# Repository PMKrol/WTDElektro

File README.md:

# WTDElektro
Scripts and software for laptops

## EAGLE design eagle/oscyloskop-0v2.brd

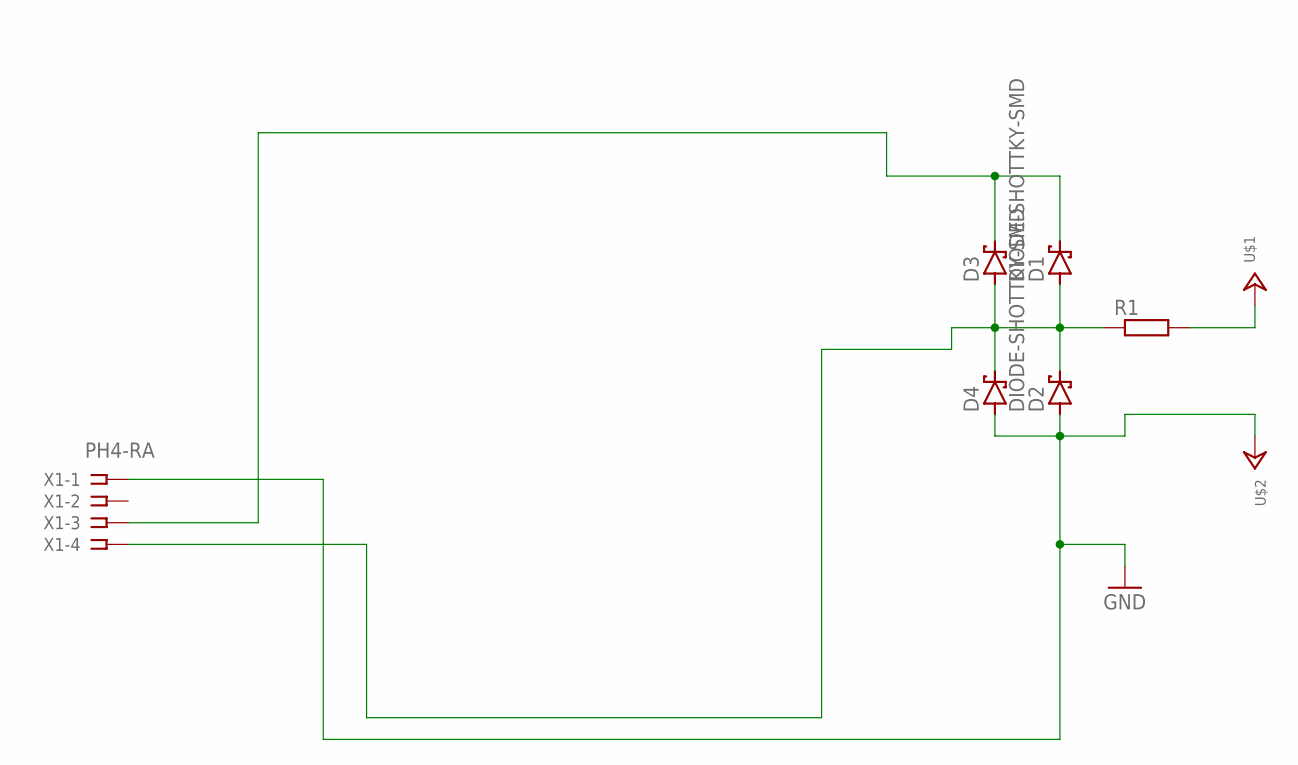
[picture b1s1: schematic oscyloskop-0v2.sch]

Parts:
D1, D2: DIODE-SHOTTKY-THT; DO41-7.6
D3, D4: DIODE-SHOTTKY-SMD; SOD123
R1: R0204/7; 0204/7
U$1, U$2: CON-BANANA; BANANA
X1: PH4-RA; SSW-104-02-G-S-RA

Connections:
GND: D2.A, D4.A, U$2.P$1, X1.1
unnamed: D1.C, D3.C, X1.3
unnamed: D1.A, D2.C, D3.A, D4.C, R1.1, X1.4
unnamed: R1.2, U$1.P$1

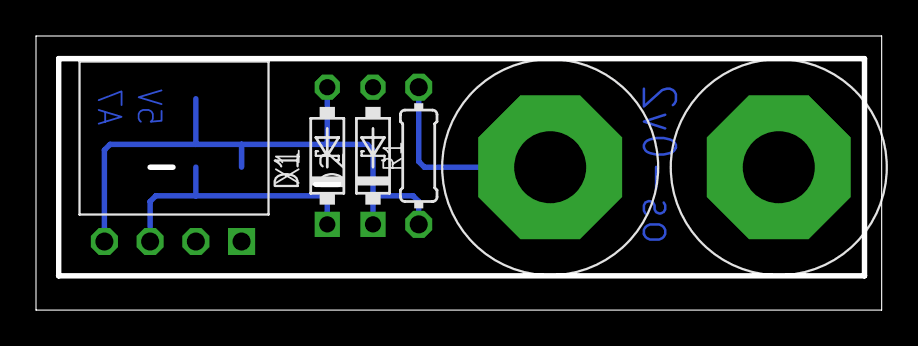
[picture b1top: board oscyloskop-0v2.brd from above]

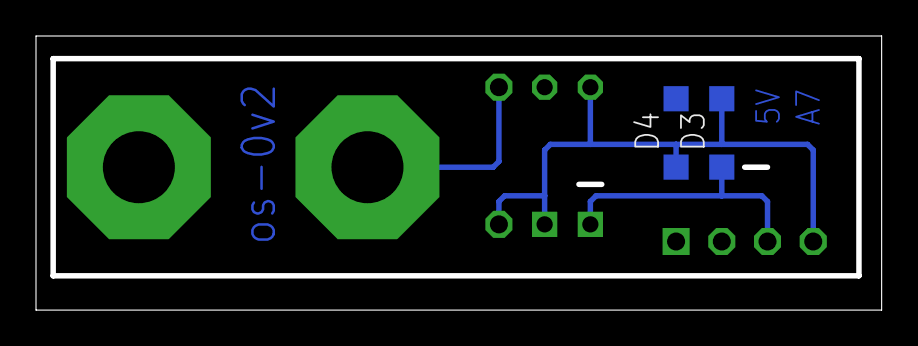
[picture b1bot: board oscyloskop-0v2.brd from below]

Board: 2 copper layers, 46.7 x 14.9 mm, 8 parts (2 on the bottom side), 4 nets.

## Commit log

2022-12-16 Add files via upload
    Original instruction from https://www.hackster.io/Ameduino/diy-arduino-oscilloscope-844fa3
2022-12-16 Add files via upload
    Eagle schematics. Libraries available at: https://github.com/PMKrol/WTDAutomatyka/tree/main/EAGLE/libraries
2022-12-16 Add files via upload
    Arduino nano case for oscilloscope.
2022-12-16 Create dummy
